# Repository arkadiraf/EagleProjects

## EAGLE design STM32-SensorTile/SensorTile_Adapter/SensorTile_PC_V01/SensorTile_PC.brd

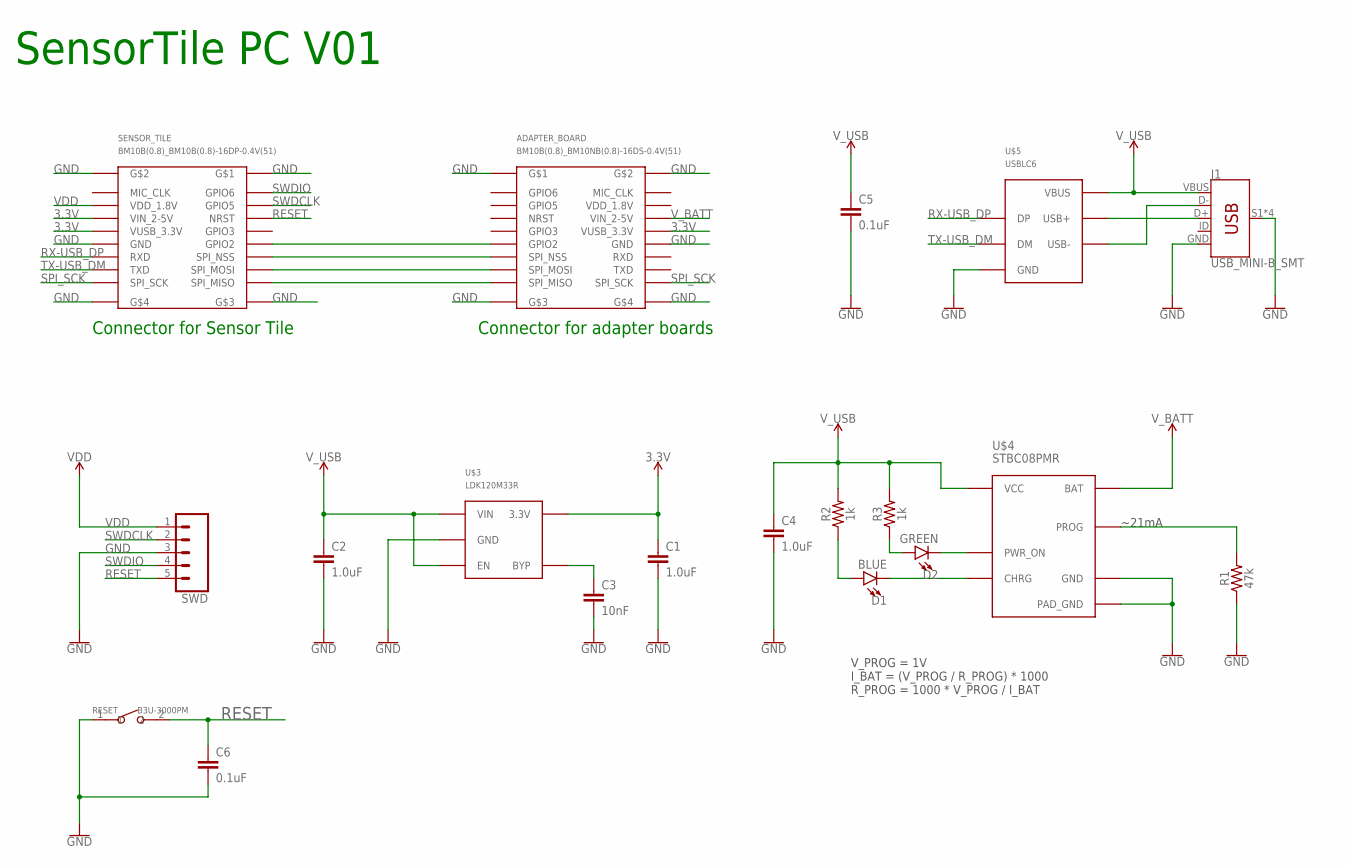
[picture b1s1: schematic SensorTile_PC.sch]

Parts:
ADAPTER_BOARD: BM10B(0.8)_BM10NB(0.8)-16DS-0.4V(51)
C1, C2, C4: 1.0uF; 0603
C3: 10nF; 0603
C5, C6: 0.1uF; 0603
D1: BLUE; LED-0603
D2: GREEN; LED-0603
J1: USB_MINI-B_SMT; USB-MINIB
R1: 47k; 0603
R2, R3: 1k; 0603
RESET: B3U-3000PM; SW2-2.6-3.0X2.5X1.2+0.4MM
SENSOR_TILE: BM10B(0.8)_BM10B(0.8)-16DP-0.4V(51)
SWD: CONN_05; 1X05
U$3: LDK120M33R; SOT23-5
U$4: STBC08PMR; 6-DFN(3X3)
U$5: USBLC6; SOT23-6L

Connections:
3.3V: ADAPTER_BOARD.VUSB_3.3V, C1.1, SENSOR_TILE.VIN_2-5V, SENSOR_TILE.VUSB_3.3V, U$3.3V3&5 (3.3V)
GND: ADAPTER_BOARD.G$1, ADAPTER_BOARD.G$2, ADAPTER_BOARD.G$3, ADAPTER_BOARD.G$4, ADAPTER_BOARD.GND$1 (GND), C1.2, C2.2, C3.2, C4.2, C5.2, C6.2, J1.GND, J1.S1 (SHIELD), J1.S2 (SHIELD), J1.S3 (SHIELD), J1.S4 (SHIELD), R1.1, RESET.1, SENSOR_TILE.G$1, SENSOR_TILE.G$2, SENSOR_TILE.G$3, SENSOR_TILE.G$4, SENSOR_TILE.GND$1 (GND), SWD.3, U$3.GND$2 (GND), U$4.GND$4 (GND), U$4.PAD_GND$7 (PAD_GND), U$5.GND$2 (GND)
unnamed: R1.2, U$4.PROG$5 (PROG)
unnamed: J1.D+, U$5.D+OUT$1$6 (USB+)
unnamed: J1.D-, U$5.D-OUT$1$4 (USB-)
unnamed: D2.C, U$4.ON$2 (PWR_ON)
unnamed: D1.C, U$4.CHRG$3 (CHRG)
unnamed: C3.1, U$3.BYP$4 (BYP)
unnamed: D1.A, R2.1
unnamed: D2.A, R3.1
unnamed: ADAPTER_BOARD.GPIO2, SENSOR_TILE.GPIO2
unnamed: ADAPTER_BOARD.SPI_NSS, SENSOR_TILE.SPI_NSS
unnamed: ADAPTER_BOARD.SPI_MOSI, SENSOR_TILE.SPI_MOSI
unnamed: ADAPTER_BOARD.SPI_MISO, SENSOR_TILE.SPI_MISO
RESET: C6.1, RESET.2, SENSOR_TILE.NRST, SWD.5
RX-USB_DP: SENSOR_TILE.RXD, U$5.D+IN$1 (DP)
SPI_SCK: ADAPTER_BOARD.SPI_SCK, SENSOR_TILE.SPI_SCK
SWDCLK: SENSOR_TILE.GPIO5, SWD.2
SWDIO: SENSOR_TILE.GPIO6, SWD.4
TX-USB_DM: SENSOR_TILE.TXD, U$5.D-IN$3 (DM)
VDD: SENSOR_TILE.VDD_1.8V, SWD.1
V_BATT: ADAPTER_BOARD.VIN_2-5V, U$4.BAT$1 (BAT)
V_USB: C2.1, C4.1, C5.1, J1.VBUS, R2.2, R3.2, U$3.EN$3 (EN), U$3.VIN$1 (VIN), U$4.VCC$6 (VCC), U$5.VUSB$5 (VBUS)

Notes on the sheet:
SensorTile PC V01
V_PROG = 1V I_BAT = (V_PROG / R_PROG) * 1000 R_PROG = 1000 * V_PROG / I_BAT
~21mA
Connector for adapter boards
Connector for Sensor Tile

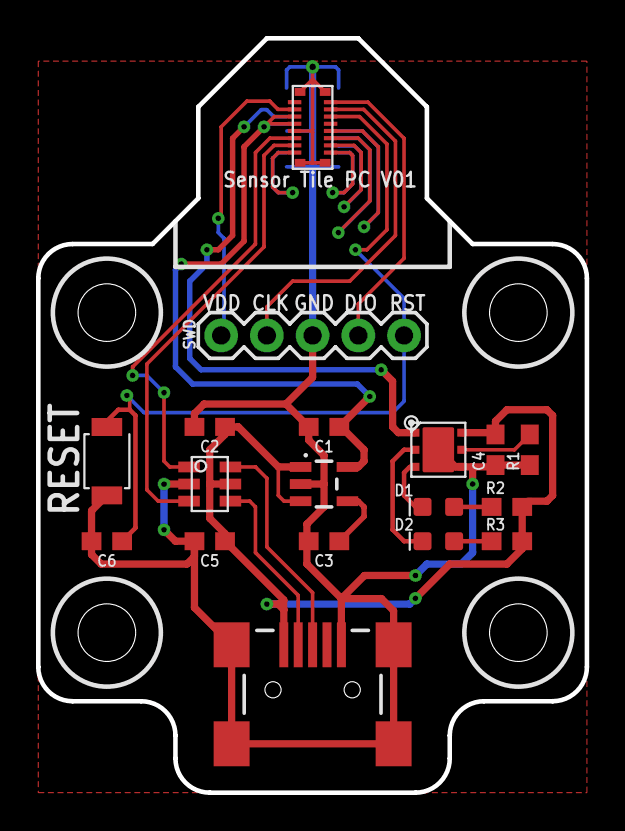
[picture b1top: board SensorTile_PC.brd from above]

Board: 2 copper layers, 30.5 x 41.9 mm, 19 parts (1 on the bottom side), 23 nets.

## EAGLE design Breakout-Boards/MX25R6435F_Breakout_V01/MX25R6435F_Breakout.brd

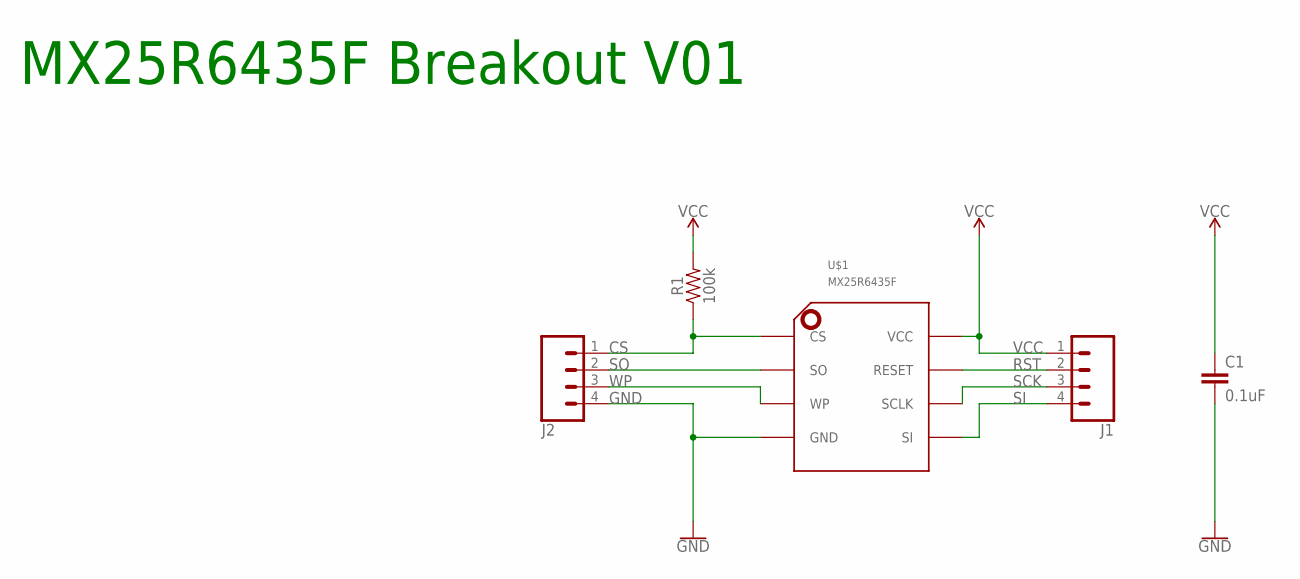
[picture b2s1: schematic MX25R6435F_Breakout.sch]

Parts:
C1: 0.1uF; 0603
J1, J2: CONN_04; 1X04
R1: 100k; 0603
U$1: MX25R6435F; 8-USON_MX25R6435F

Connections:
CS: J2.1, R1.1, U$1.CS$1 (CS)
GND: C1.2, J2.4, U$1.GND$4 (GND)
RST: J1.2, U$1.RESET$7 (RESET)
SCK: J1.3, U$1.SCLK$6 (SCLK)
SI: J1.4, U$1.SI$5 (SI)
SO: J2.2, U$1.SO$2 (SO)
VCC: C1.1, J1.1, R1.2, U$1.VCC$8 (VCC)
WP: J2.3, U$1.WP$3 (WP)

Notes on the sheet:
MX25R6435F Breakout V01

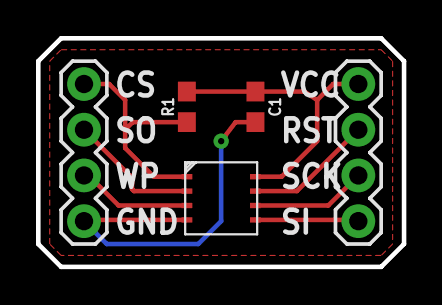
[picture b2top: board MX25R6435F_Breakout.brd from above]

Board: 2 copper layers, 20.3 x 12.7 mm, 5 parts (0 on the bottom side), 8 nets.

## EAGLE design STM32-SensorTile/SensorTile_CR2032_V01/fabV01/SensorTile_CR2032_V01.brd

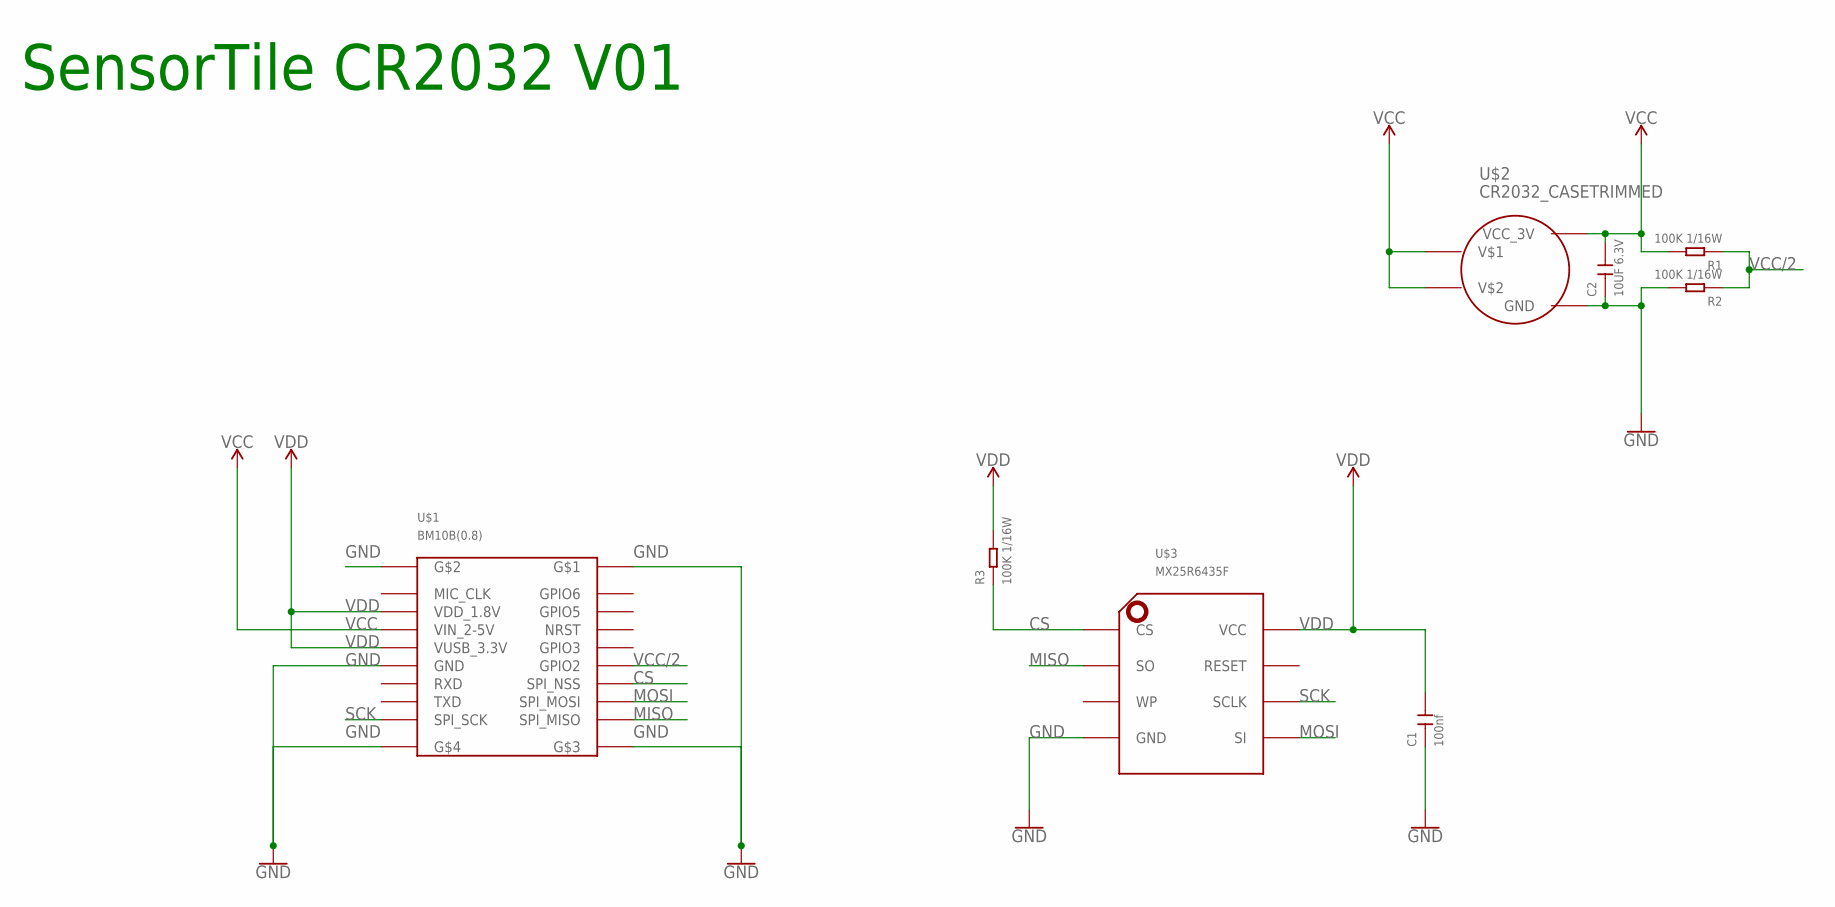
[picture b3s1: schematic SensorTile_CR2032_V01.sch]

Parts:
C1: 100nf; C0402
C2: 10UF 6.3V; C0603
R1, R2, R3: 100K 1/16W; R0402
U$1: BM10B(0.8); BM10B(0.8)-16DP-0.4V(51)
U$2: CR2032_CASETRIMMED; CR2032_CASE_TRIMMED
U$3: MX25R6435F; 8-USON_MX25R6435F

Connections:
CS: R3.1, U$1.SPI_NSS, U$3.CS$1 (CS)
GND: C1.1, C2.1, R2.2, U$1.G$1, U$1.G$2, U$1.G$3, U$1.G$4, U$1.GND$1 (GND), U$2.GND, U$3.GND$4 (GND)
MISO: U$1.SPI_MISO, U$3.SO$2 (SO)
MOSI: U$1.SPI_MOSI, U$3.SI$5 (SI)
SCK: U$1.SPI_SCK, U$3.SCLK$6 (SCLK)
VCC: C2.2, R1.2, U$1.VIN_2-5V, U$2.VCC@1, U$2.VCC@2, U$2.VCC_3V
VCC/2: R1.1, R2.1, U$1.GPIO2
VDD: C1.2, R3.2, U$1.VDD_1.8V, U$1.VUSB_3.3V, U$3.VCC$8 (VCC)

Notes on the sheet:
SensorTile CR2032 V01

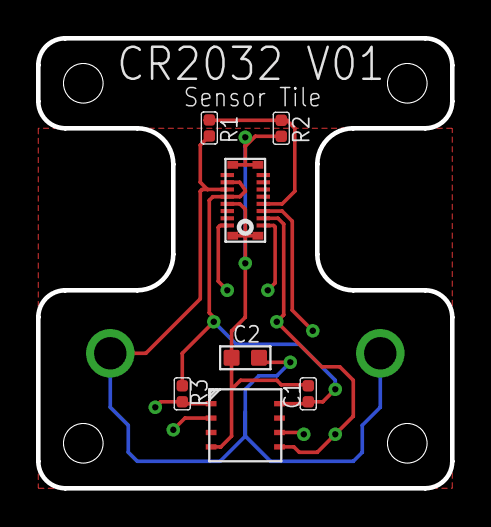
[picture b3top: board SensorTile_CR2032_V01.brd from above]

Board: 4 copper layers, 23.0 x 25.0 mm, 8 parts (1 on the bottom side), 8 nets.

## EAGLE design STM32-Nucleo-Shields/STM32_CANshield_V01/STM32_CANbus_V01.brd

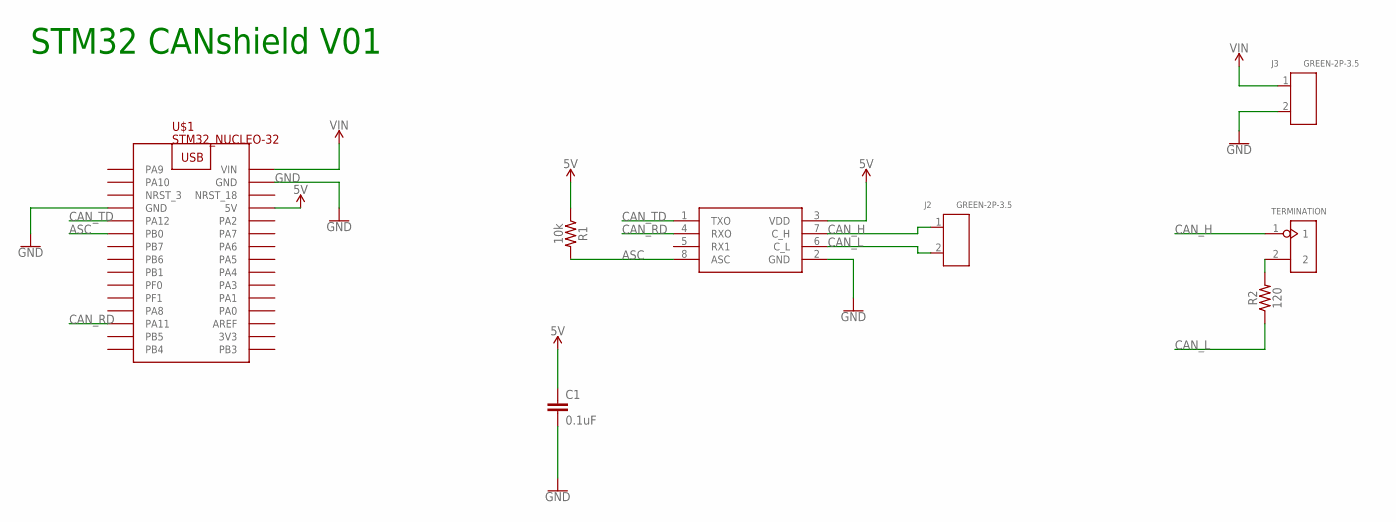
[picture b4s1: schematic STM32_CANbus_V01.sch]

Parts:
C: L9616; SO8
C1: 0.1uF; 0805
J2, J3: GREEN-2P-3.5; H2-3.5-7.0X7.0MM
R1: 10k; 0805
R2: 120; 1206
TERMINATION: DIP-BLACK-JUMPER; H2-2.54
U$1: STM32_NUCLEO-32

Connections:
3V3: U$1.3V3
5V: C.3 (VDD), C1.1, R1.1, U$1.5V
ASC: C.8 (ASC), R1.2, U$1.PB0
CAN_H: C.7 (C_H), J2.1, TERMINATION.1
CAN_L: C.6 (C_L), J2.2, R2.1
CAN_RD: C.4 (RXO), U$1.PA11
CAN_TD: C.1 (TXO), U$1.PA12
GND: C.2 (GND), C1.2, J3.2, U$1.GND@4 (GND), U$1.GND@17 (GND)
unnamed: R2.2, TERMINATION.2
VIN: J3.1, U$1.VIN

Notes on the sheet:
STM32 CANshield V01

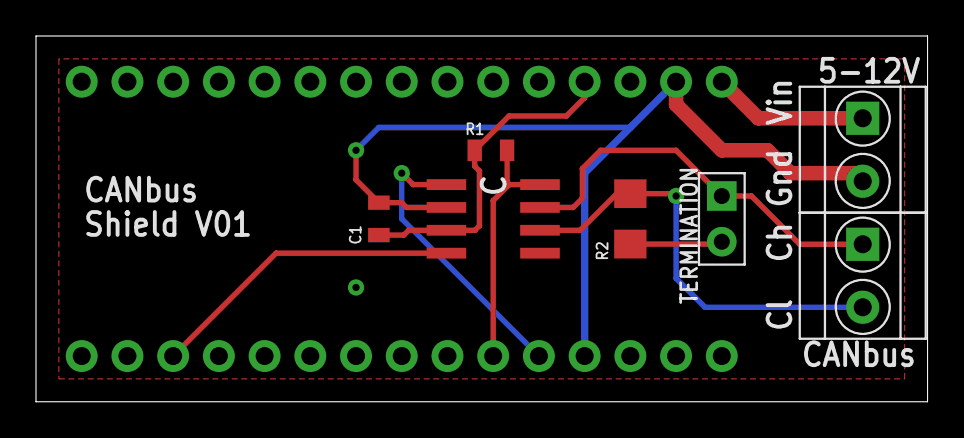
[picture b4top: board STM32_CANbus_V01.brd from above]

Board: 2 copper layers, 49.5 x 20.3 mm, 8 parts (1 on the bottom side), 9 nets.

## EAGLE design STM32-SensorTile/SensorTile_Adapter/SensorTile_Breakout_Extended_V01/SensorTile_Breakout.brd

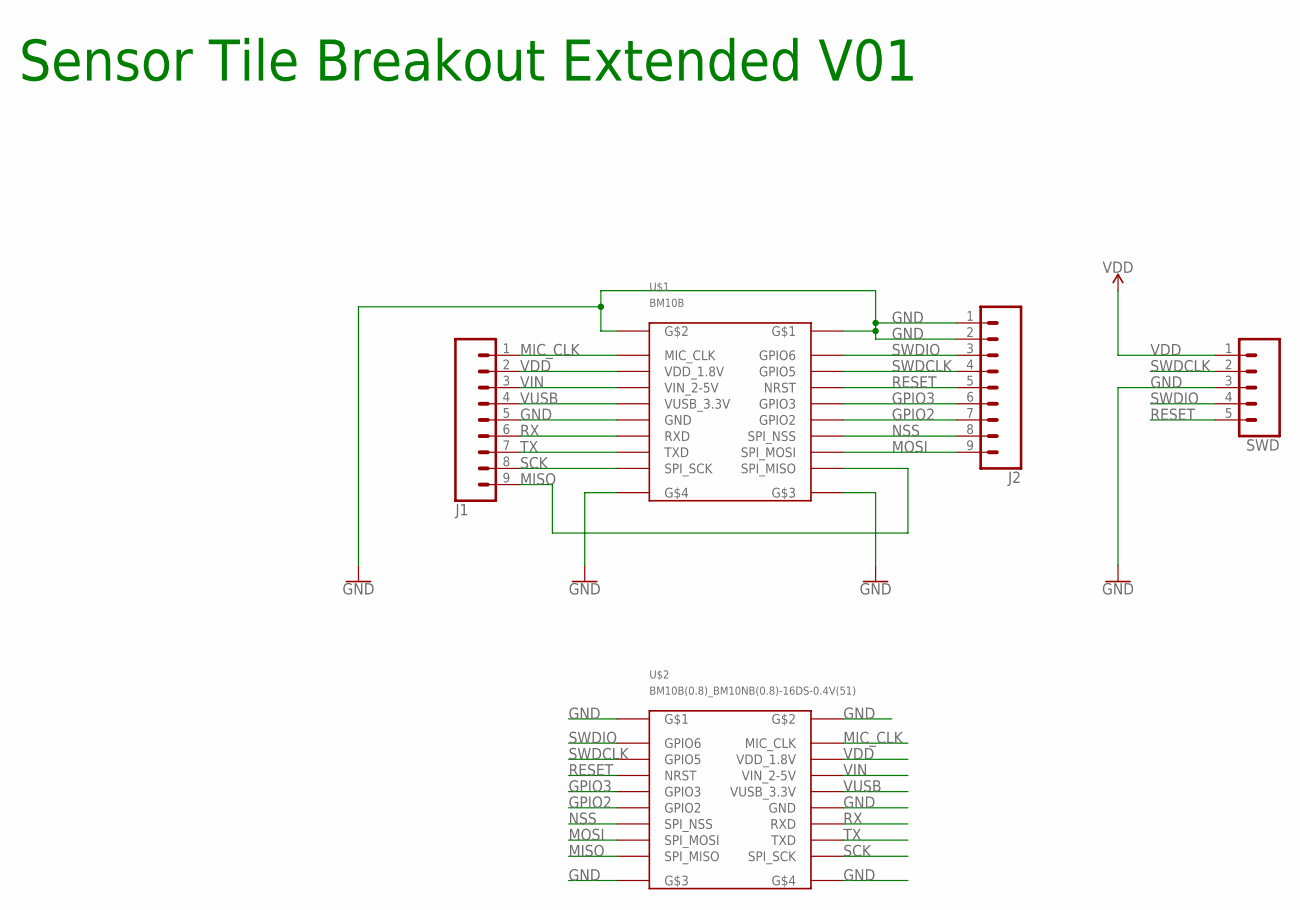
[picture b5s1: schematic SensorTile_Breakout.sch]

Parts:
J1, J2: CONN_09; 1X09
SWD: CONN_05; 1X05
U$1: BM10B; BM10B(0.8)-16DP-0.4V(51)
U$2: BM10B(0.8)_BM10NB(0.8)-16DS-0.4V(51)

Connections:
GND: J1.5, J2.1, J2.2, SWD.3, U$1.G$1, U$1.G$2, U$1.G$3, U$1.G$4, U$1.GND$1 (GND), U$2.G$1, U$2.G$2, U$2.G$3, U$2.G$4, U$2.GND$1 (GND)
GPIO2: J2.7, U$1.GPIO2, U$2.GPIO2
GPIO3: J2.6, U$1.GPIO3, U$2.GPIO3
MIC_CLK: J1.1, U$1.MIC_CLK, U$2.MIC_CLK
MISO: J1.9, U$1.SPI_MISO, U$2.SPI_MISO
MOSI: J2.9, U$1.SPI_MOSI, U$2.SPI_MOSI
NSS: J2.8, U$1.SPI_NSS, U$2.SPI_NSS
RESET: J2.5, SWD.5, U$1.NRST, U$2.NRST
RX: J1.6, U$1.RXD, U$2.RXD
SCK: J1.8, U$1.SPI_SCK, U$2.SPI_SCK
SWDCLK: J2.4, SWD.2, U$1.GPIO5, U$2.GPIO5
SWDIO: J2.3, SWD.4, U$1.GPIO6, U$2.GPIO6
TX: J1.7, U$1.TXD, U$2.TXD
VDD: J1.2, SWD.1, U$1.VDD_1.8V, U$2.VDD_1.8V
VIN: J1.3, U$1.VIN_2-5V, U$2.VIN_2-5V
VUSB: J1.4, U$1.VUSB_3.3V, U$2.VUSB_3.3V

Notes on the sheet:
Sensor Tile Breakout Extended V01

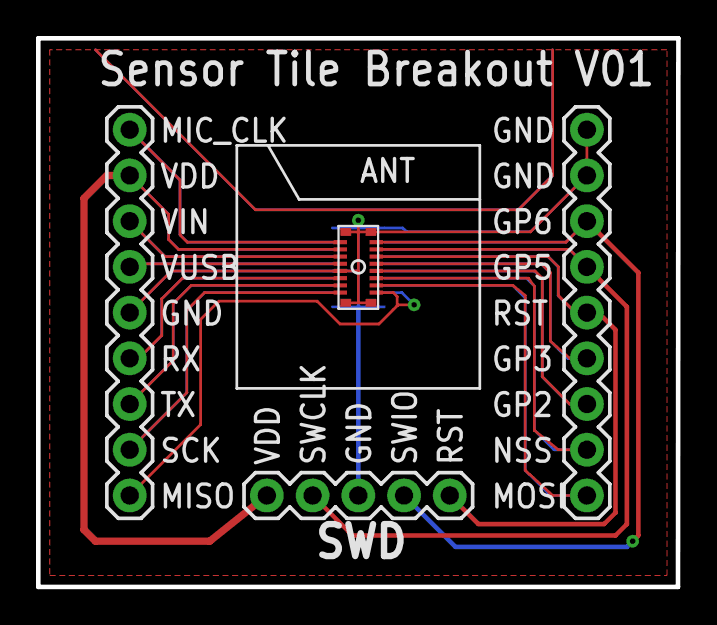
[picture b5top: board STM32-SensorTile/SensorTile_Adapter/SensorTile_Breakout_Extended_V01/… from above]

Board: 2 copper layers, 35.6 x 30.5 mm, 5 parts (1 on the bottom side), 16 nets.

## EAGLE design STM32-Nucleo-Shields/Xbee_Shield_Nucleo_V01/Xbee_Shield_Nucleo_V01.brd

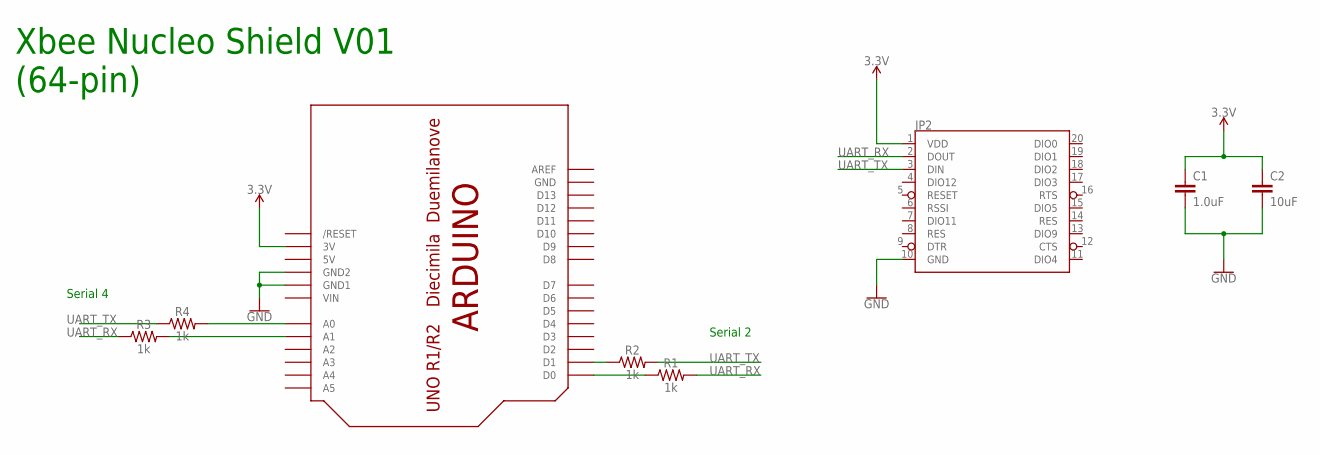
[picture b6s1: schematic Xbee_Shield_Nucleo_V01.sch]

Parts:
C1: 1.0uF; 0805
C2: 10uF; 0805
JP2: XBEESILK; XBEE-SILK
R1, R2, R3, R4: 1k; 0805
U1: ARDUINO-NOHOLE

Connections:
3.3V: C1.1, C2.1, JP2.1 (VDD), U1.3V
5V: U1.5V
GND: C1.2, C2.2, JP2.10 (GND), U1.GND, U1.GND1, U1.GND2
unnamed: R1.1, U1.D0
unnamed: R2.1, U1.D1
unnamed: R4.2, U1.A0
unnamed: R3.2, U1.A1
UART_RX: JP2.2 (DOUT), R1.2, R3.1
UART_TX: JP2.3 (DIN), R2.2, R4.1
VIN: U1.VIN

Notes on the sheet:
Xbee Nucleo Shield V01 (64-pin)
Serial 4
Serial 2

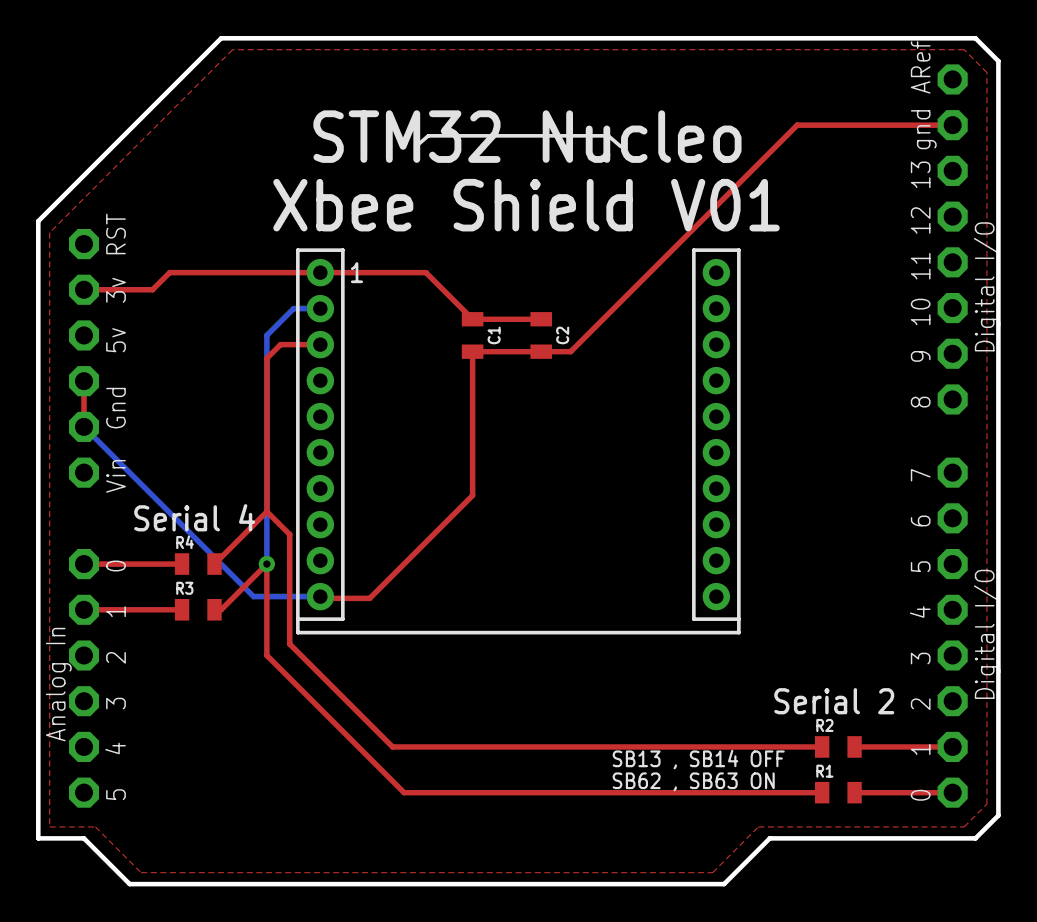
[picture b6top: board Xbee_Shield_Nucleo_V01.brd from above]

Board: 2 copper layers, 53.3 x 47.0 mm, 8 parts (0 on the bottom side), 8 nets.

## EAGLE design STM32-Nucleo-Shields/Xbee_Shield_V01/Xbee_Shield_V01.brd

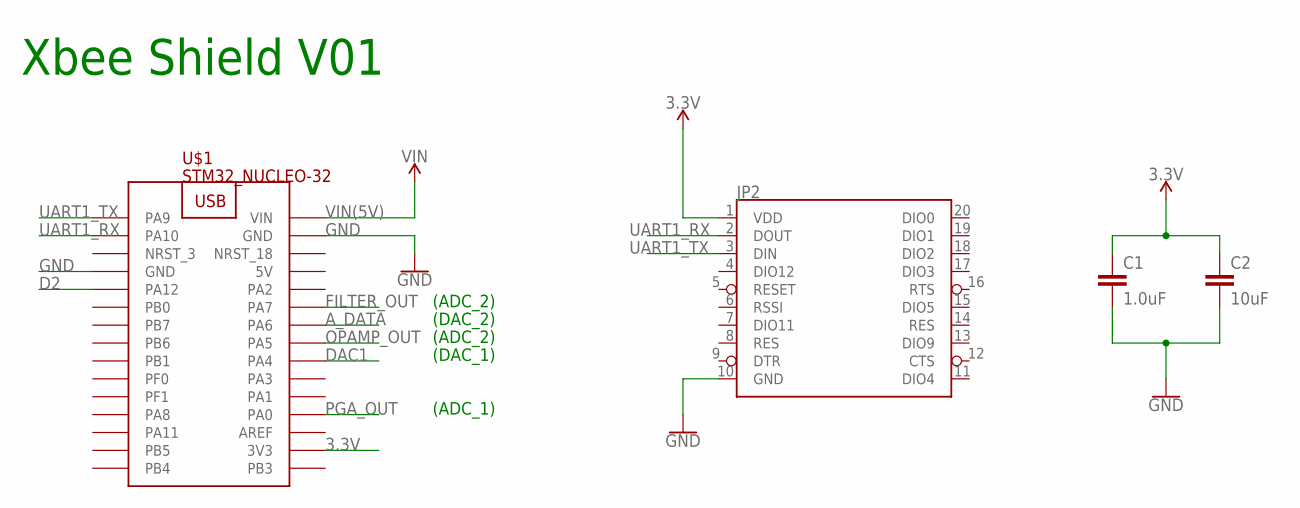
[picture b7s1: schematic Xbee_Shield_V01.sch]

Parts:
C1: 1.0uF; 0805
C2: 10uF; 0805
JP2: XBEESILK; XBEE-SILK
U$1: STM32_NUCLEO-32

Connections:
3.3V: C1.1, C2.1, JP2.1 (VDD), U$1.3V3
5V: U$1.5V
A_DATA: U$1.PA6
D2: U$1.PA12
DAC1: U$1.PA4
FILTER_OUT: U$1.PA7
GND: C1.2, C2.2, JP2.10 (GND), U$1.GND@4 (GND), U$1.GND@17 (GND)
OPAMP_OUT: U$1.PA5
PGA_OUT: U$1.PA0
UART1_RX: JP2.2 (DOUT), U$1.PA10
UART1_TX: JP2.3 (DIN), U$1.PA9
VIN(5V): U$1.VIN

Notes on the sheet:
Xbee Shield V01
(ADC_1)
(ADC_2)
(DAC_1)
(DAC_2)

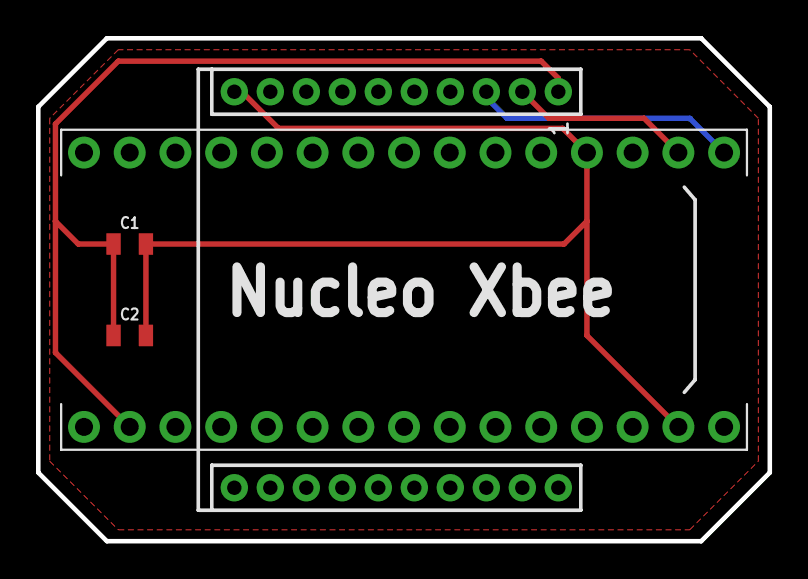
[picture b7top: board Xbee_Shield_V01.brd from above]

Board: 2 copper layers, 40.6 x 27.9 mm, 4 parts (0 on the bottom side), 4 nets.

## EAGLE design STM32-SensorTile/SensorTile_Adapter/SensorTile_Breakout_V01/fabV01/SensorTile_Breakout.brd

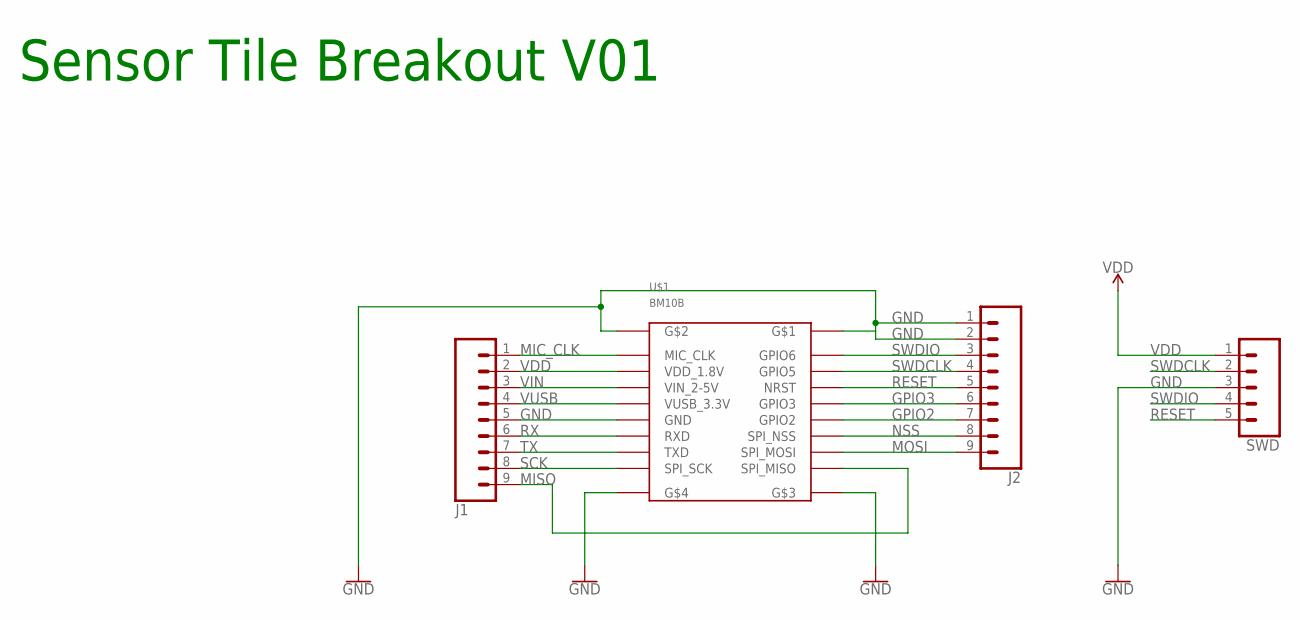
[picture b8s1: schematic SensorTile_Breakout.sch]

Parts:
J1, J2: CONN_09; 1X09
SWD: CONN_05; 1X05
U$1: BM10B; BM10B(0.8)-16DP-0.4V(51)

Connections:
GND: J1.5, J2.1, J2.2, SWD.3, U$1.G$1, U$1.G$2, U$1.G$3, U$1.G$4, U$1.GND$1 (GND)
GPIO2: J2.7, U$1.GPIO2
GPIO3: J2.6, U$1.GPIO3
MIC_CLK: J1.1, U$1.MIC_CLK
MISO: J1.9, U$1.SPI_MISO
MOSI: J2.9, U$1.SPI_MOSI
NSS: J2.8, U$1.SPI_NSS
RESET: J2.5, SWD.5, U$1.NRST
RX: J1.6, U$1.RXD
SCK: J1.8, U$1.SPI_SCK
SWDCLK: J2.4, SWD.2, U$1.GPIO5
SWDIO: J2.3, SWD.4, U$1.GPIO6
TX: J1.7, U$1.TXD
VDD: J1.2, SWD.1, U$1.VDD_1.8V
VIN: J1.3, U$1.VIN_2-5V
VUSB: J1.4, U$1.VUSB_3.3V

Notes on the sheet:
Sensor Tile Breakout V01

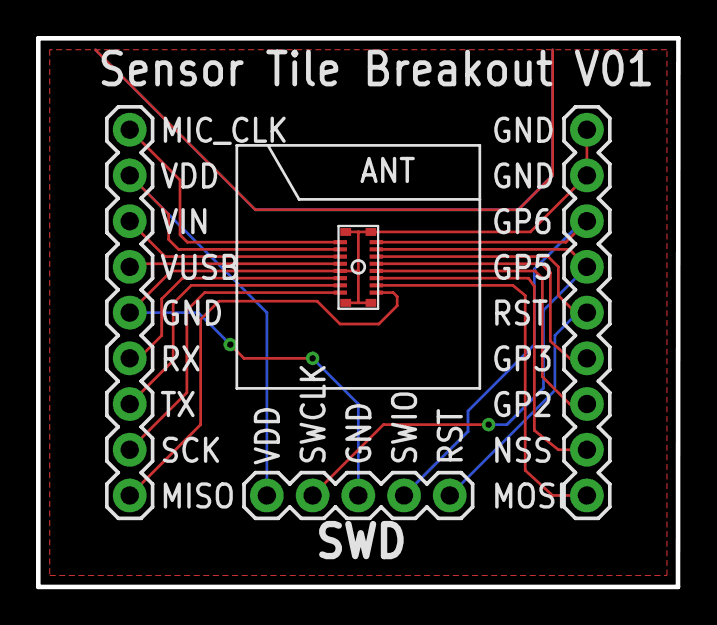
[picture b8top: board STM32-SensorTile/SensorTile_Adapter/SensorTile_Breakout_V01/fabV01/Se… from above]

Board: 2 copper layers, 35.6 x 30.5 mm, 4 parts (0 on the bottom side), 16 nets.

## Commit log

2019-02-14 Initial_Commit
2019-02-14 added images
2019-03-19 added pdfs for can shield

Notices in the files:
parts and their libraries:
SparkFun-Capacitors: Licensing: Creative Commons ShareAlike 4.0 International - https://creativecommons.org/licenses/by-sa/4.0
